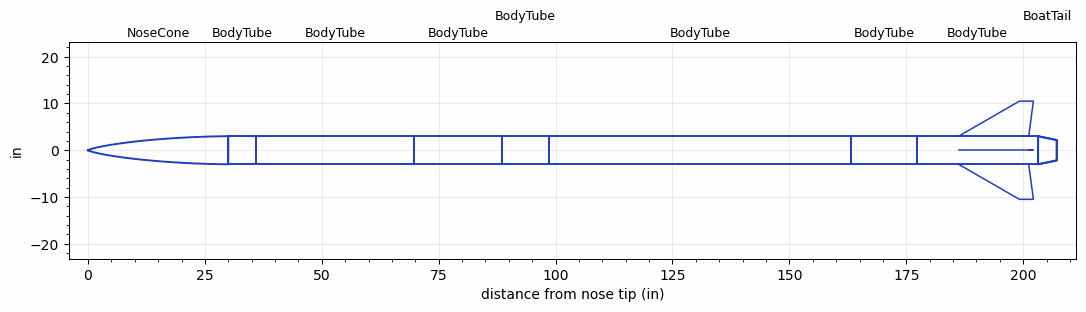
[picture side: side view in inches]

<RASAeroDocument>
 <FileVersion>2</FileVersion>
 <RocketDesign>
  <NoseCone>
   <Length>30</Length>
   <Diameter>6</Diameter>
   <Shape>LV-Haack</Shape>
   <Location>0</Location>
  </NoseCone>
  <BodyTube>
   <Length>6</Length>
   <Diameter>6</Diameter>
   <Location>30</Location>
  </BodyTube>
  <BodyTube>
   <Length>33.8</Length>
   <Diameter>6</Diameter>
   <Location>36</Location>
  </BodyTube>
  <BodyTube>
   <Length>18.7</Length>
   <Diameter>6</Diameter>
   <Location>69.8</Location>
  </BodyTube>
  <BodyTube>
   <Length>10</Length>
   <Diameter>6</Diameter>
   <Location>88.5</Location>
  </BodyTube>
  <BodyTube>
   <Length>64.69</Length>
   <Diameter>6</Diameter>
   <Location>98.5</Location>
  </BodyTube>
  <BodyTube>
   <Length>14</Length>
   <Diameter>6</Diameter>
   <Location>163.19</Location>
  </BodyTube>
  <BodyTube>
   <Length>26</Length>
   <Diameter>6</Diameter>
   <Location>177.19</Location>
   <BoattailLength>4</BoattailLength>
   <BoattailRearDiameter>4.36</BoattailRearDiameter>
   <Fin>
    <Count>4</Count>
    <Chord>15</Chord>
    <Span>7.5</Span>
    <SweepDistance>13</SweepDistance>
    <TipChord>3</TipChord>
    <Thickness>0.3</Thickness>
    <LERadius>0.01</LERadius>
    <Location>17</Location>
    <AirfoilSection>Hexagonal</AirfoilSection>
    <FX1>0.3</FX1>
    <FX3>0.3</FX3>
   </Fin>
  </BodyTube>
  <BoatTail>
   <Length>4</Length>
   <Diameter>6</Diameter>
   <RearDiameter>4.36</RearDiameter>
   <Location>203.19</Location>
  </BoatTail>
  <Surface>Camouflage Paint</Surface>
  <ModifiedBarrowman>True</ModifiedBarrowman>
  <Turbulence>True</Turbulence>
  <UseBooster1>False</UseBooster1>
  <UseBooster2>False</UseBooster2>
 </RocketDesign>
 <LaunchSite>
  <Altitude>2950</Altitude>
  <Pressure>27</Pressure>
  <RodAngle>6</RodAngle>
  <RodLength>32.8</RodLength>
  <Temperature>86</Temperature>
  <WindSpeed>16</WindSpeed>
 </LaunchSite>
 <Recovery>
  <Altitude1>1000</Altitude1>
  <Altitude2>1000</Altitude2>
  <DeviceType1>None</DeviceType1>
  <DeviceType2>None</DeviceType2>
  <Event1>False</Event1>
  <Event2>False</Event2>
  <Size1>1</Size1>
  <Size2>1</Size2>
  <EventType1>None</EventType1>
  <EventType2>None</EventType2>
  <CD1>1.33</CD1>
  <CD2>1.33</CD2>
 </Recovery>
 <SimulationList>
  <Simulation>
   <SustainerEngine>TRIAL  (TAMUSRT)</SustainerEngine>
   <SustainerLaunchWt>143</SustainerLaunchWt>
   <SustainerNozzleDiameter>3.424</SustainerNozzleDiameter>
   <SustainerCG>131</SustainerCG>
   <SustainerIgnitionDelay>0</SustainerIgnitionDelay>
   <Booster1SeparationDelay>0</Booster1SeparationDelay>
   <Booster1IgnitionDelay>0</Booster1IgnitionDelay>
   <IncludeBooster1>False</IncludeBooster1>
   <Booster2Delay>0</Booster2Delay>
   <IncludeBooster2>False</IncludeBooster2>
   <TimetoApogee>47.688</TimetoApogee>
   <MaxAltitude>35294.7</MaxAltitude>
   <MaxVelocity>1754.217</MaxVelocity>
  </Simulation>
  <Simulation>
   <SustainerEngine>COMB_PLUS  (TAMUSRT)</SustainerEngine>
   <SustainerLaunchWt>128</SustainerLaunchWt>
   <SustainerCG>125</SustainerCG>
   <SustainerIgnitionDelay>0</SustainerIgnitionDelay>
   <Booster1SeparationDelay>0</Booster1SeparationDelay>
   <Booster1IgnitionDelay>0</Booster1IgnitionDelay>
   <IncludeBooster1>False</IncludeBooster1>
   <Booster2Delay>0</Booster2Delay>
   <IncludeBooster2>False</IncludeBooster2>
   <TimetoApogee>41.71901</TimetoApogee>
   <MaxAltitude>26628.62</MaxAltitude>
   <MaxVelocity>1520.361</MaxVelocity>
  </Simulation>
  <Simulation>
   <SustainerEngine>COMBINED_30  (TAMUSRT)</SustainerEngine>
   <SustainerLaunchWt>149</SustainerLaunchWt>
   <SustainerCG>130</SustainerCG>
   <SustainerIgnitionDelay>0</SustainerIgnitionDelay>
   <Booster1SeparationDelay>0</Booster1SeparationDelay>
   <Booster1IgnitionDelay>0</Booster1IgnitionDelay>
   <IncludeBooster1>False</IncludeBooster1>
   <Booster2Delay>0</Booster2Delay>
   <IncludeBooster2>False</IncludeBooster2>
  </Simulation>
  <Simulation>
   <SustainerEngine>CUST  (TAMUSRT)</SustainerEngine>
   <SustainerLaunchWt>152</SustainerLaunchWt>
   <SustainerCG>132</SustainerCG>
   <SustainerIgnitionDelay>0</SustainerIgnitionDelay>
   <Booster1SeparationDelay>0</Booster1SeparationDelay>
   <Booster1IgnitionDelay>0</Booster1IgnitionDelay>
   <IncludeBooster1>False</IncludeBooster1>
   <Booster2Delay>0</Booster2Delay>
   <IncludeBooster2>False</IncludeBooster2>
   <TimetoApogee>45.99829</TimetoApogee>
   <MaxAltitude>31779.34</MaxAltitude>
   <MaxVelocity>1582.848</MaxVelocity>
  </Simulation>
  <Simulation>
   <SustainerEngine>TRIAL  (TAMUSRT)</SustainerEngine>
   <SustainerLaunchWt>143</SustainerLaunchWt>
   <SustainerNozzleDiameter>3.5</SustainerNozzleDiameter>
   <SustainerCG>131</SustainerCG>
   <SustainerIgnitionDelay>0</SustainerIgnitionDelay>
   <Booster1SeparationDelay>0</Booster1SeparationDelay>
   <Booster1IgnitionDelay>0</Booster1IgnitionDelay>
   <IncludeBooster1>False</IncludeBooster1>
   <Booster2Delay>0</Booster2Delay>
   <IncludeBooster2>False</IncludeBooster2>
   <TimetoApogee>47.78799</TimetoApogee>
   <MaxAltitude>35467.81</MaxAltitude>
   <MaxVelocity>1758.893</MaxVelocity>
  </Simulation>
 </SimulationList>
</RASAeroDocument>
